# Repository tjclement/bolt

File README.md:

# A new tool to break stuff! ⚒️

The Curious Bolt is a security multi-tool for getting started with hardware hacking. It is simultaneously:
- a programmable crowbar **voltage glitcher** ⚡️
- an **8-channel logic analyzer** 👩‍💻
- and a simple differential power analysis **oscilloscope**. 📉

## How do you turn this on?
See [the docs](https://bolt.curious.supplies/docs) for how to set up and use your Bolt.

## Acknowledgements
PulseView scope code by [Jaroslav Kysela](https://github.com/perexg/picoprobe-sump), extended to run in parallel with other functions by Joris Witteman (MIT License)

Software and hardware design by [Joris Witteman](https://github.com/jorisplusplus) for Curious Supplies (MIT License)

PCB art by [ankhaneko.art](https://ankhaneko.art) for Curious Supplies

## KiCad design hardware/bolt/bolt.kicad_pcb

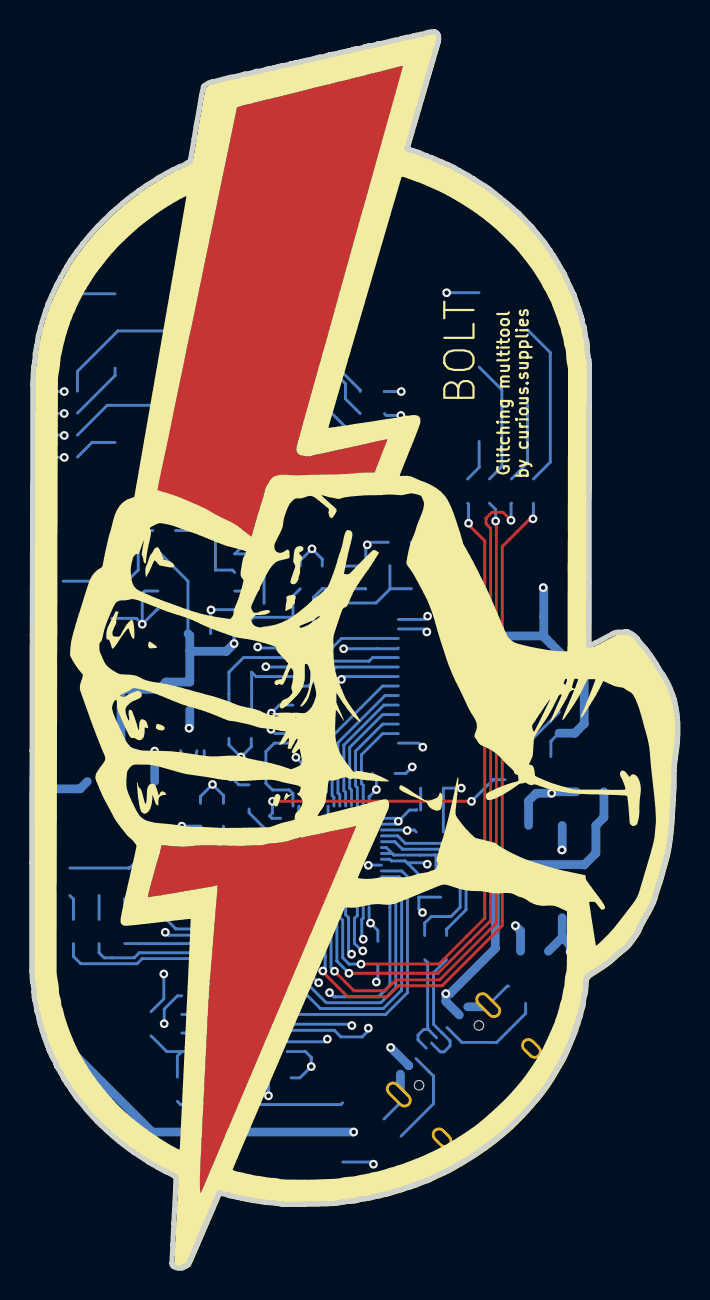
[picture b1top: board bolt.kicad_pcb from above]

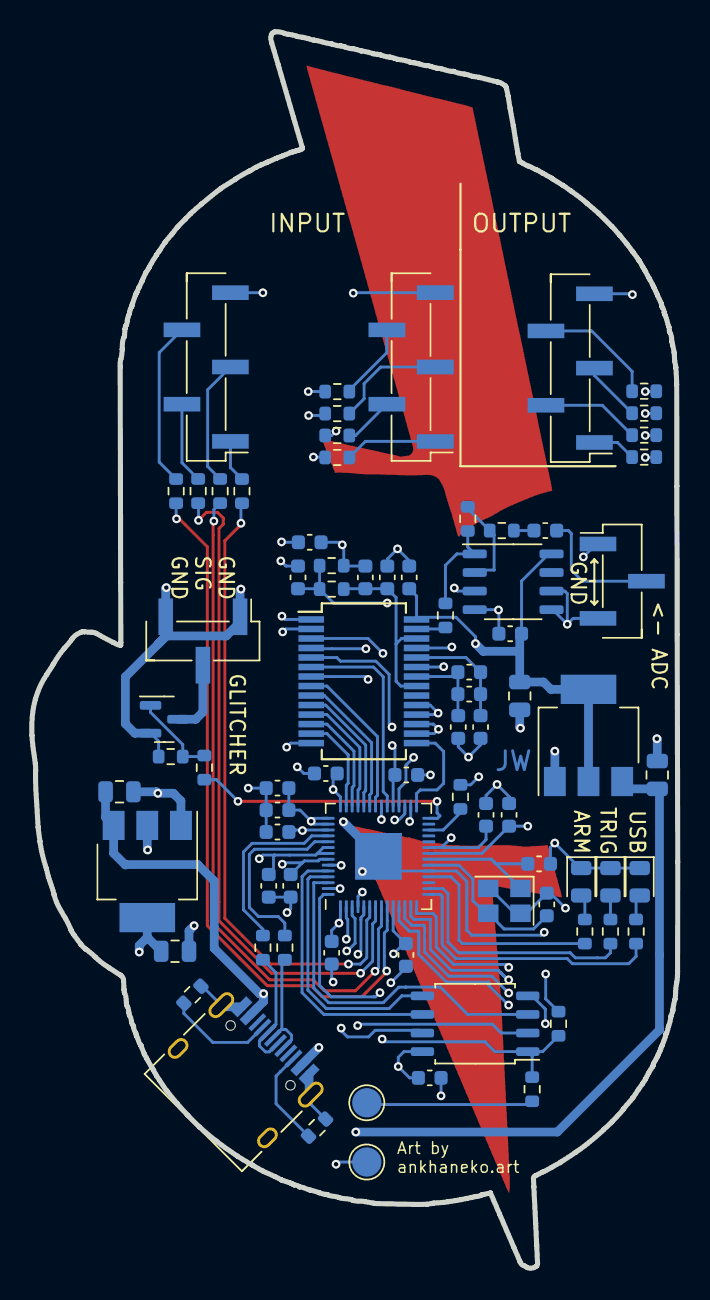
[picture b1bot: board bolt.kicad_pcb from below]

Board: 4 copper layers, 44.1 x 84.5 mm, 77 parts (77 on the bottom side), 75 nets.

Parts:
C1, C2, C17, C18: 22uF; C_0805_2012Metric
C3, C4, C6, C7, C8, C9, C10, C11, C12, C14, C19, C20, C21, C24, C25, C26, C27, C28: 100nF; C_0603_1608Metric
C5, C13, C22, C29: 1uF; C_0603_1608Metric
C15, C16: 27pF; C_0603_1608Metric
C23: 10uF; C_0603_1608Metric
D1: LED RED; LED_0805_2012Metric
D2, D3: LED YELLOW; LED_0805_2012Metric
J1: USB_C_Receptacle_USB2.0; USB_C_Receptacle_HRO_TYPE-C-31-M-12
J3, J4, J6: Conn_01x05; PinHeader_1x05_P2.54mm_Vertical_SMD_Pin1Left
J5, J7: Conn_01x03; PinHeader_1x03_P2.54mm_Vertical_SMD_Pin1Left
Q1: AO3400; SOT-23
R1, R2, R8, R31: 5.1k; R_0603_1608Metric
R3, R4: 27.4; R_0603_1608Metric
R5, R7, R22: 1k; R_0603_1608Metric
R6: dnf; R_0603_1608Metric
R9, R13, R14: 470; R_0603_1608Metric
R10, R17, R18, R19, R20, R23, R24, R25, R26, R27, R28, R29, R30: 270; R_0603_1608Metric
R11: 27; R_0603_1608Metric
R12, R21: 10; R_0603_1608Metric
TP1, TP2: TestPoint; TestPoint_Pad_D2.0mm
U1: RP2040; QFN-56-1EP_7x7mm_P0.4mm_EP3.2x3.2mm
U2, U4: AMS1117-3.3; SOT-223-3_TabPin2
U3: W25Q128JVS; SOIC-8_5.23x5.23mm_P1.27mm
U5: COS722SR; SOP-8_3.9x4.9mm_P1.27mm
U6: MS9280; SSOP-28_5.3x10.2mm_P0.65mm
Y1: 12MHz; Crystal_SMD_3225-4Pin_3.2x2.5mm

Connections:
+1V1: C3.1, C4.1, C5.1, U1.23 (DVDD), U1.45 (VREG_VOUT), U1.50 (DVDD)
+3.3V: C2.1, C6.1, C7.1, C8.1, C9.1, C10.1, C11.1, C12.1, C13.1, C14.1, C28.1, R5.2, R6.2, U1.1 (IOVDD), U1.10 (IOVDD), U1.22 (IOVDD), U1.33 (IOVDD), U1.42 (IOVDD), U1.43 (ADC_AVDD), U1.44 (VREG_IN), U1.48 (USB_VDD), U1.49 (IOVDD), U2.2 (VO), U3.8 (VCC), U6.2 (DRVDD)
+3.3VA: C18.1, C19.1, C27.1, U4.2 (VO), U5.8 (V+), U6.23 (MODE), U6.28 (AVDD)
+5V: C1.1, C17.1, J1.A4 (VBUS), J1.A9 (VBUS), J1.B4 (VBUS), J1.B9 (VBUS), U2.3 (VI), U4.3 (VI)
/CLK: U1.29 (GPIO18), U6.15 (CLK)
/D0: U1.30 (GPIO19), U6.3 (D0)
/D1: U1.31 (GPIO20), U6.4 (D1)
/D2: U1.32 (GPIO21), U6.5 (D2)
/D3: U1.34 (GPIO22), U6.6 (D3)
/D4: U1.35 (GPIO23), U6.7 (D4)
/D5: U1.36 (GPIO24), U6.8 (D5)
/D6: U1.37 (GPIO25), U6.9 (D6)
/D7: U1.38 (GPIO26_ADC0), U6.10 (D7)
/D8: U1.39 (GPIO27_ADC1), U6.11 (D8)
/D9: U1.40 (GPIO28_ADC2), U6.12 (D9)
/OTR: U1.41 (GPIO29_ADC3), U6.13 (OTR)
D+: J1.A6 (D+), J1.B6 (D+), R3.1
D-: J1.A7 (D-), J1.B7 (D-), R4.1
GND: C1.2, C2.2, C3.2, C4.2, C5.2, C6.2, C7.2, C8.2, C9.2, C10.2, C11.2, C12.2, C13.2, C14.2, C15.2, C16.2, C17.2, C18.2, C19.2, C21.2, C22.2, C25.2, C26.2, C27.2, C28.2, C29.2, D1.1 (K), D2.1 (K), D3.1 (K), J1.A1 (GND), J1.A12 (GND), J1.B1 (GND), J1.B12 (GND), J1.S1 (SHIELD), J3.5, J4.5, J5.1, J5.3, J6.5, J7.1, J7.3, Q1.2 (S), R1.1, R2.1, R8.1, R22.1, TP1.1, U1.19 (TESTEN), U1.57 (GND), U2.1 (GND), U3.4 (GND), U4.1 (GND), U5.4 (V-), U5.5 (+), U5.6 (-), U6.1 (AVSS), U6.14 (DRVSS), U6.16 (TRISTATE), U6.17 (STBY), U6.18 (REFSENSE), U6.19 (CLAMP), U6.25 (REFBS), Y1.2, Y1.4
unnamed: C20.2, R11.2
unnamed: D1.2 (A), R13.1
unnamed: D2.2 (A), R14.1
unnamed: D3.2 (A), R9.1
unnamed: J1.A5 (CC1), R2.2
unnamed: J1.B5 (CC2), R1.2
unnamed: J3.1, R26.1
unnamed: J3.2, R25.1
unnamed: J3.3, R24.1
unnamed: J3.4, R23.1
unnamed: J4.1, R30.1
unnamed: J4.2, R29.1
unnamed: J4.3, R28.1
unnamed: J4.4, R27.1
unnamed: C20.1, J5.2
unnamed: J6.1, R20.1
unnamed: J6.2, R19.1
unnamed: J6.3, R18.1
unnamed: J6.4, R17.1
unnamed: J7.2, Q1.3 (D)
unnamed: Q1.1 (G), R21.1, R22.2
unnamed: R7.2, TP2.1
unnamed: R10.1, R12.2, U5.1
unnamed: R30.2, U1.2 (GPIO0)
unnamed: R29.2, U1.3 (GPIO1)
unnamed: R28.2, U1.4 (GPIO2)
unnamed: R27.2, U1.5 (GPIO3)
unnamed: R26.2, U1.6 (GPIO4)
unnamed: R25.2, U1.7 (GPIO5)
unnamed: R24.2, U1.8 (GPIO6)
unnamed: R23.2, U1.9 (GPIO7)
unnamed: R20.2, U1.11 (GPIO8)
unnamed: R19.2, U1.12 (GPIO9)
unnamed: R18.2, U1.13 (GPIO10)
unnamed: R17.2, U1.14 (GPIO11)
unnamed: R13.2, U1.15 (GPIO12)
unnamed: R14.2, U1.16 (GPIO13)
unnamed: R9.2, U1.18 (GPIO15)
unnamed: R21.2, U1.28 (GPIO17)
unnamed: U1.52 (QSPI_SCLK), U3.6 (CLK)
unnamed: U1.53 (QSPI_SD0), U3.5 (DI(IO0))
unnamed: U1.55 (QSPI_SD1), U3.2 (DO(IO1))
unnamed: U1.54 (QSPI_SD2), U3.3 (IO2)
unnamed: U1.51 (QSPI_SD3), U3.7 (IO3)
unnamed: R6.1, R7.1, U1.56 (QSPI_SS), U3.1 (~CS)
unnamed: R5.1, U1.26 (RUN)
unnamed: R4.2, U1.46 (USB_DM)
unnamed: R3.2, U1.47 (USB_DP)
unnamed: C15.1, U1.20 (XIN), Y1.3
unnamed: C16.1, U1.21 (XOUT), Y1.1
unnamed: C29.1, R8.2, R31.1, U5.3 (+)
unnamed: R10.2, R11.1, U5.2 (-)
unnamed: R12.1, U6.27 (AIN)
unnamed: C23.2, C24.2, C25.1, U6.24 (REFBF)
unnamed: C23.1, C24.1, C26.1, U6.22 (REFTF)
unnamed: C21.1, C22.1, R31.2, U6.21 (REFTS), U6.26 (VREF)

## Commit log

2023-10-25 Docs go live
2023-10-25 Fixed udev docs
2023-10-25 Simplified udev docs
2023-10-25 Tweaked readme
2023-10-25 Fixed link in acknowledgements
2023-10-26 Appended prog I/O docs
2024-01-08 Added scope data plotting, added bootloader reboot command for updating firmware, made get_last_trace() return floats in Volt by default
2024-01-25 Fixed issue on Mac OS where USB interface selection wasn't consistent across OS versions
2024-02-01 Added gold release Bolt firmware
2024-02-01 Added Bolt hardware design
2024-02-01 Linked to docs site
